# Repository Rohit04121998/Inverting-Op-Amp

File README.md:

# Inverting-Op-Amp
This is a simple Inverting Op-Amp circuit.

The components used are

1. LM741 
2. Resistors - 10K and 100K
3. Power Supply Slots

The library for LM741 and the footprint were already present. A PCB design was made and connections were made according to the desin.

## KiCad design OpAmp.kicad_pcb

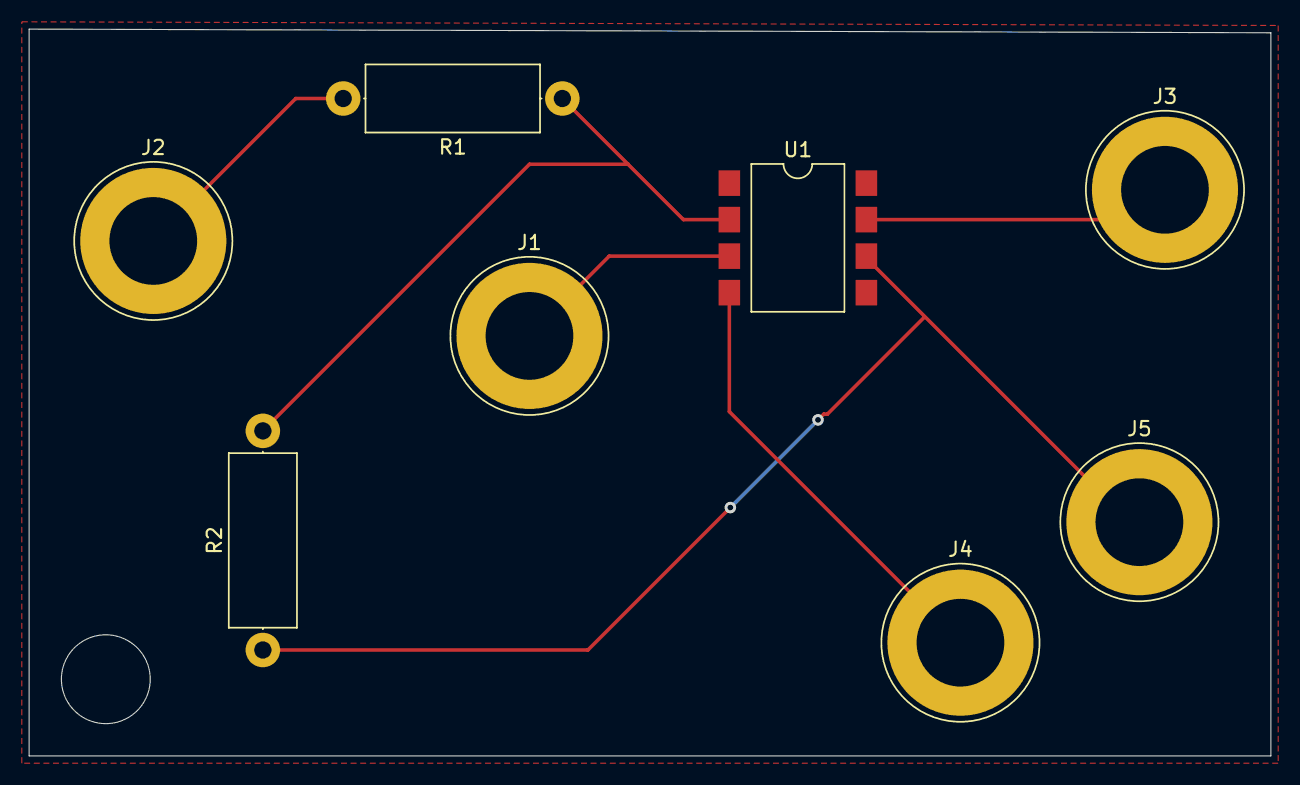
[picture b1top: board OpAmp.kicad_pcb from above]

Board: 2 copper layers, 86.4 x 50.5 mm, 8 parts (0 on the bottom side), 6 nets.

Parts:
J1: Ground; Banana_Jack_1Pin
J2: Input; Banana_Jack_1Pin
J3: +12V; Banana_Jack_1Pin
J4: -12V; Banana_Jack_1Pin
J5: Output; Banana_Jack_1Pin
R1, R2: R; R_Axial_DIN0414_L11.9mm_D4.5mm_P15.24mm_Horizontal
U1: LM741; SMDIP-8_W9.53mm_Clearance8mm

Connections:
GND: J1.1, U1.3
unnamed: J2.1, R1.2
unnamed: J3.1, U1.7
unnamed: J4.1, U1.4
unnamed: J5.1, R2.1, U1.6
unnamed: R1.1, R2.2, U1.2
